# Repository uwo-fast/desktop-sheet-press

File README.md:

# Open Source Scientific Sheet Press: General Overview

This repository contains the design assets for the publication [Open-source cold and hot scientific sheet press for investigating polymer-based material properties](https://doi.org/10.1016/j.ohx.2024.e00566), which details the development of an adaptable, open-source platform for polymer sheet pressing.".

## Description

The Open Source Scientific Sheet Press is a mechanical device engineered for converting plastic waste into flat sheets of recycled plastic. Drawing inspiration from existing models like Precious Plastics, this platform is designed with adaptability, flexibility, and sustainability as core principles. This repository contains the main resources for the design of the physical press and it's manufacturing.

## Key Features

1. **Adaptability**: Engineered to work with a diverse range of plastic materials.
2. **Scalability**: Modular design allows for easy scaling to meet various production needs.
3. **Flexibility**: Utilizes open-source and off-the-shelf components, with comprehensive documentation and multiple system topologies for customization.

## General Applications

1. **Material Recycling**: Transforms plastic waste into reusable sheets.
2. **Product Manufacturing**: Ideal for the production of flat plastic components across various applications.
3. **Research and Development**: Serves as a testbed for material properties and novel production methods.

## Future Directions

1. **5x5' Canadian Standardized Sheet Press**: This version will meet industrial standards within the province of Ontario.
2. **Expanding System Topologies**: Work is ongoing to offer more system variations based on desired specifications and features.
3. **Vacuum Forming Integration**: Plans to incorporate vacuum forming capabilities, expanding the range of products that can be manufactured from the recycled plastic sheets.
4. **Automation and Industry 4.0**: Future iterations will focus on integrating smart technologies for autonomous operation, real-time data analytics, and IoT capabilities.
5. **Comprehensive Sourcing**: Plans to provide sourcing information tailored to various locales, considering regional regulations, standards, and availability.
6. **Reengineering High-Cost Components**: Long-term goal to redesign non-open-source and expensive components to meet required standards and certifications.

## Repository Structure

This repository will include multiple iterations and variations of the sheet press, acting as a living document for continuous development and enhancements.

For detailed documentation, consult the respective folders and files within this repository.

## About the FAST Research Group

The Free Appropriate Sustainable Technology (FAST) research group, led by Professor Joshua Pearce, is based at Western University and focuses on driving sustainability innovations. The group works on a myriad of projects ranging from solar photovoltaic technology to alternative food to open-source hardware to distributed recycling and additive manufacturing (DRAM).

This Open Source Sheet Press project is an initiative led by the FAST group, aligning with our broader goals of sustainable development and open-source technology. We are focused on developing solutions that not only contribute to recycling and sustainable manufacturing but also push the boundaries of what's possible through continuous research and innovation.

For more information on the FAST group, please visit [FAST on Appropedia](https://www.appropedia.org/FAST).

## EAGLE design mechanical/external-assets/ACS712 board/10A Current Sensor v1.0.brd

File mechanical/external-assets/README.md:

# LEGAL DISCLAIMER AND LIMITATION OF LICENSING FOR "EXTERNAL-ASSETS" DIRECTORY

## SCOPE OF DISCLAIMER
This "external-assets" folder is a directory of various third-party materials — software, digital files, and other intellectual properties (hereafter "Assets"). This disclaimer serves as notice that the intellectual property rights governing these Assets are distinctly separate from the GNU General Public License v3.0 (the "Primary License") that applies to the remainder of this repository.

## EXCEPTION TO PRIMARY LICENSE
The Primary License does not extend to the Assets within this directory. Intellectual property rights of each Asset are held by their respective legal owner(s), who reserve all rights not explicitly granted. The inclusion of these Assets within this repository should not be construed as an implicit grant of rights, license, or privileges pertaining to said Assets.

## ATTRIBUTION
For each Asset, an `attribution.txt` document is be available in the respective directory. This document identifies the Asset's original source and, if available, its legal owner, along with any known or asserted intellectual property rights or usage limitations.

## CORRECTIVE MEASURES
If you are the rightful owner of an Asset and suspect a breach of your intellectual property rights within this repository, you are implored to contact the repository owner forthwith. The intent is to promptly remedy any infringement or inadequate attribution as per your rightful demands.

## ABSOLUTE DISCLAIMER OF WARRANTIES
The Assets are furnished "as is," bereft of any warranty, whether overt or implied. The repository owner disclaims all accountability and liability stemming from the use or misuse of these Assets.

## NO AFFILIATION OR ENDORSEMENT
The presence of these Assets within this repository should not be interpreted as an indication of partnership, endorsement, or affiliation between the repository owner and the legal owner(s) of the Assets. All trademarks and identifiers are employed solely for descriptive and attribution purposes.

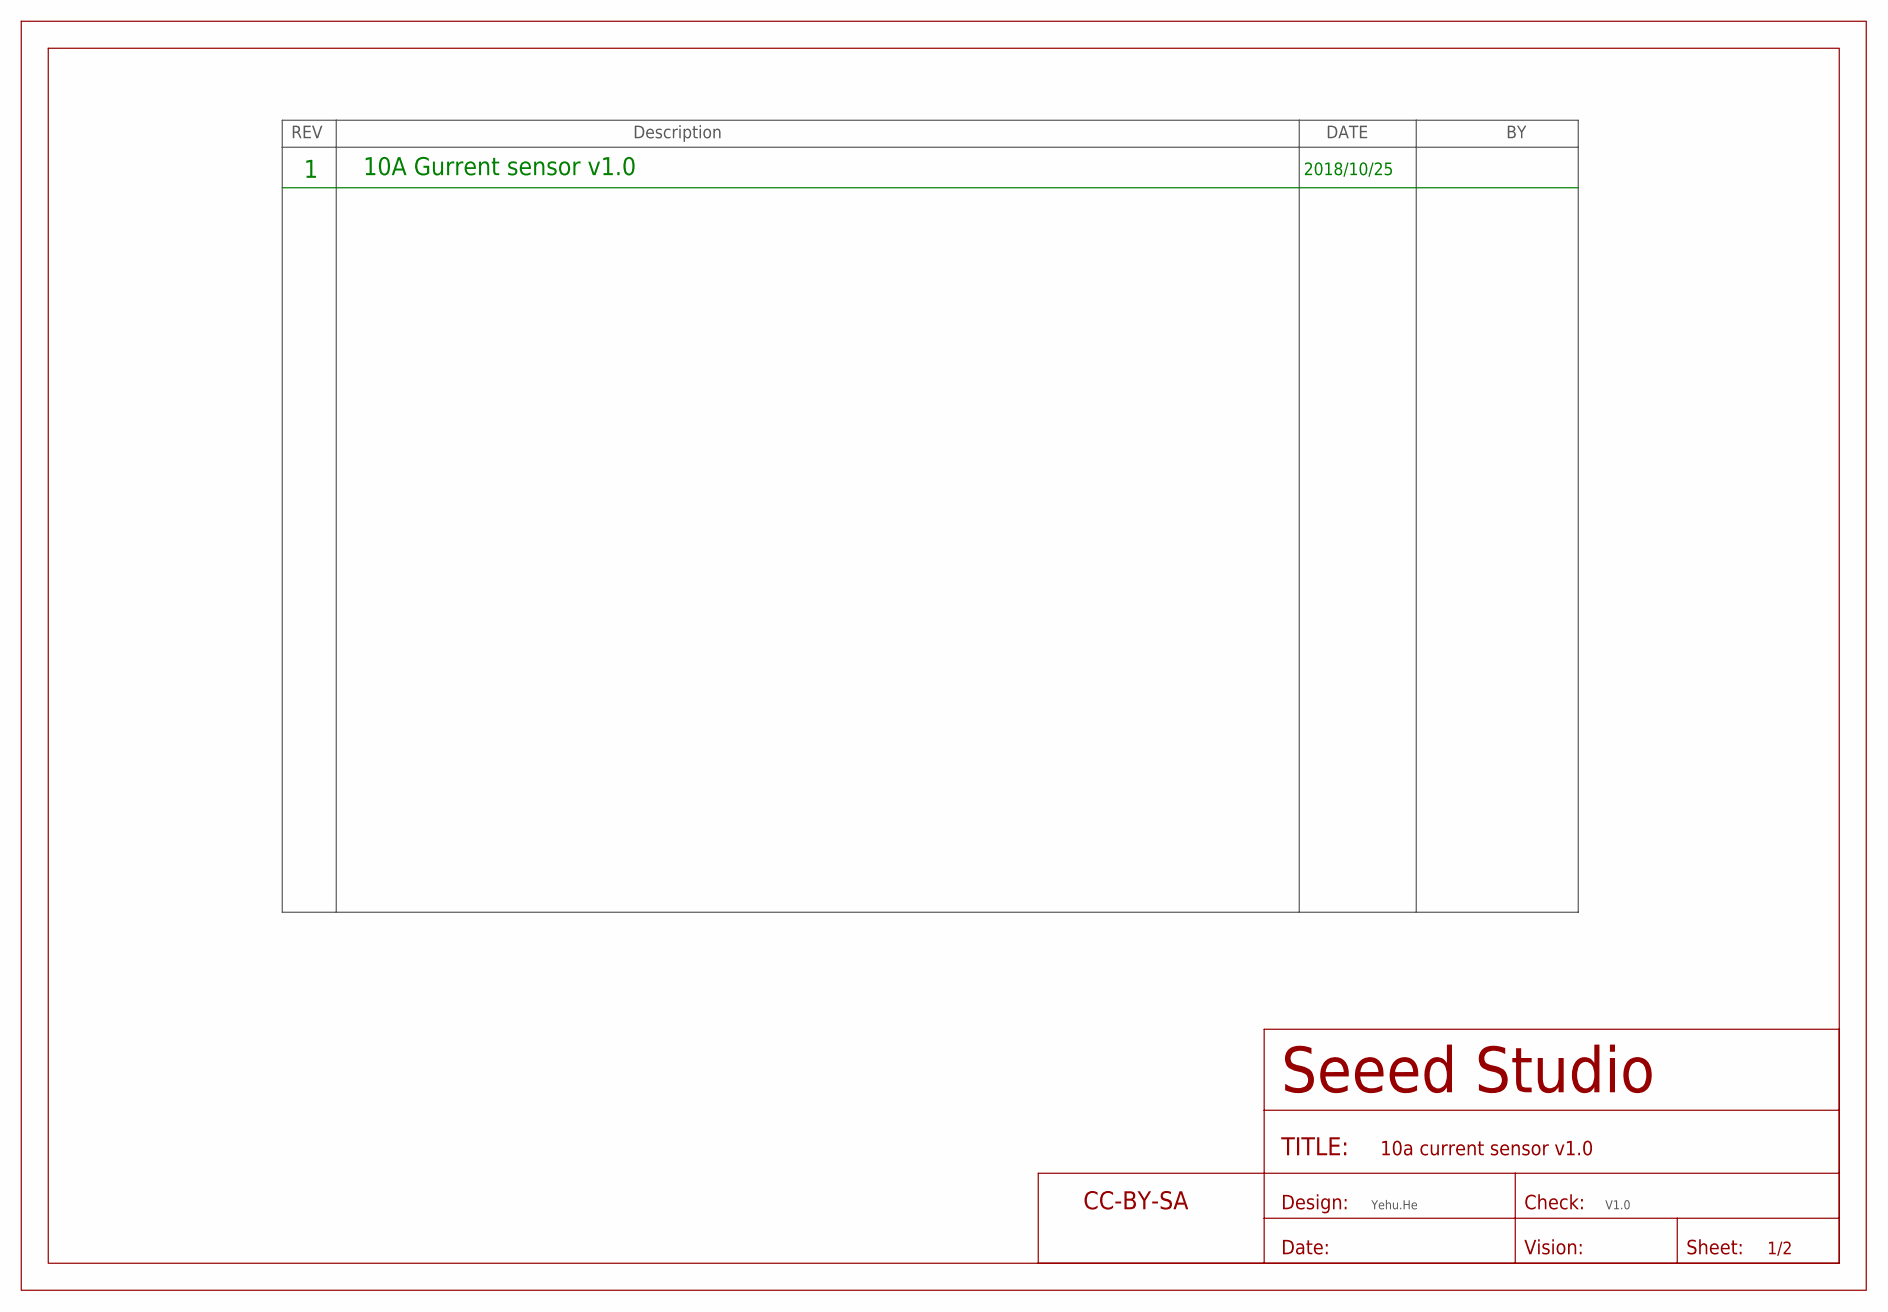
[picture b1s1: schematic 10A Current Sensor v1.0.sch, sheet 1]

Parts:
FR1: SEEEDSTUDIO-OPEN-SCH-FRAME; SEEEDSTUDIO-PCB-FRAME

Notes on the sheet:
Yehu.He
V1.0
10A Gurrent sensor v1.0
2018/10/25

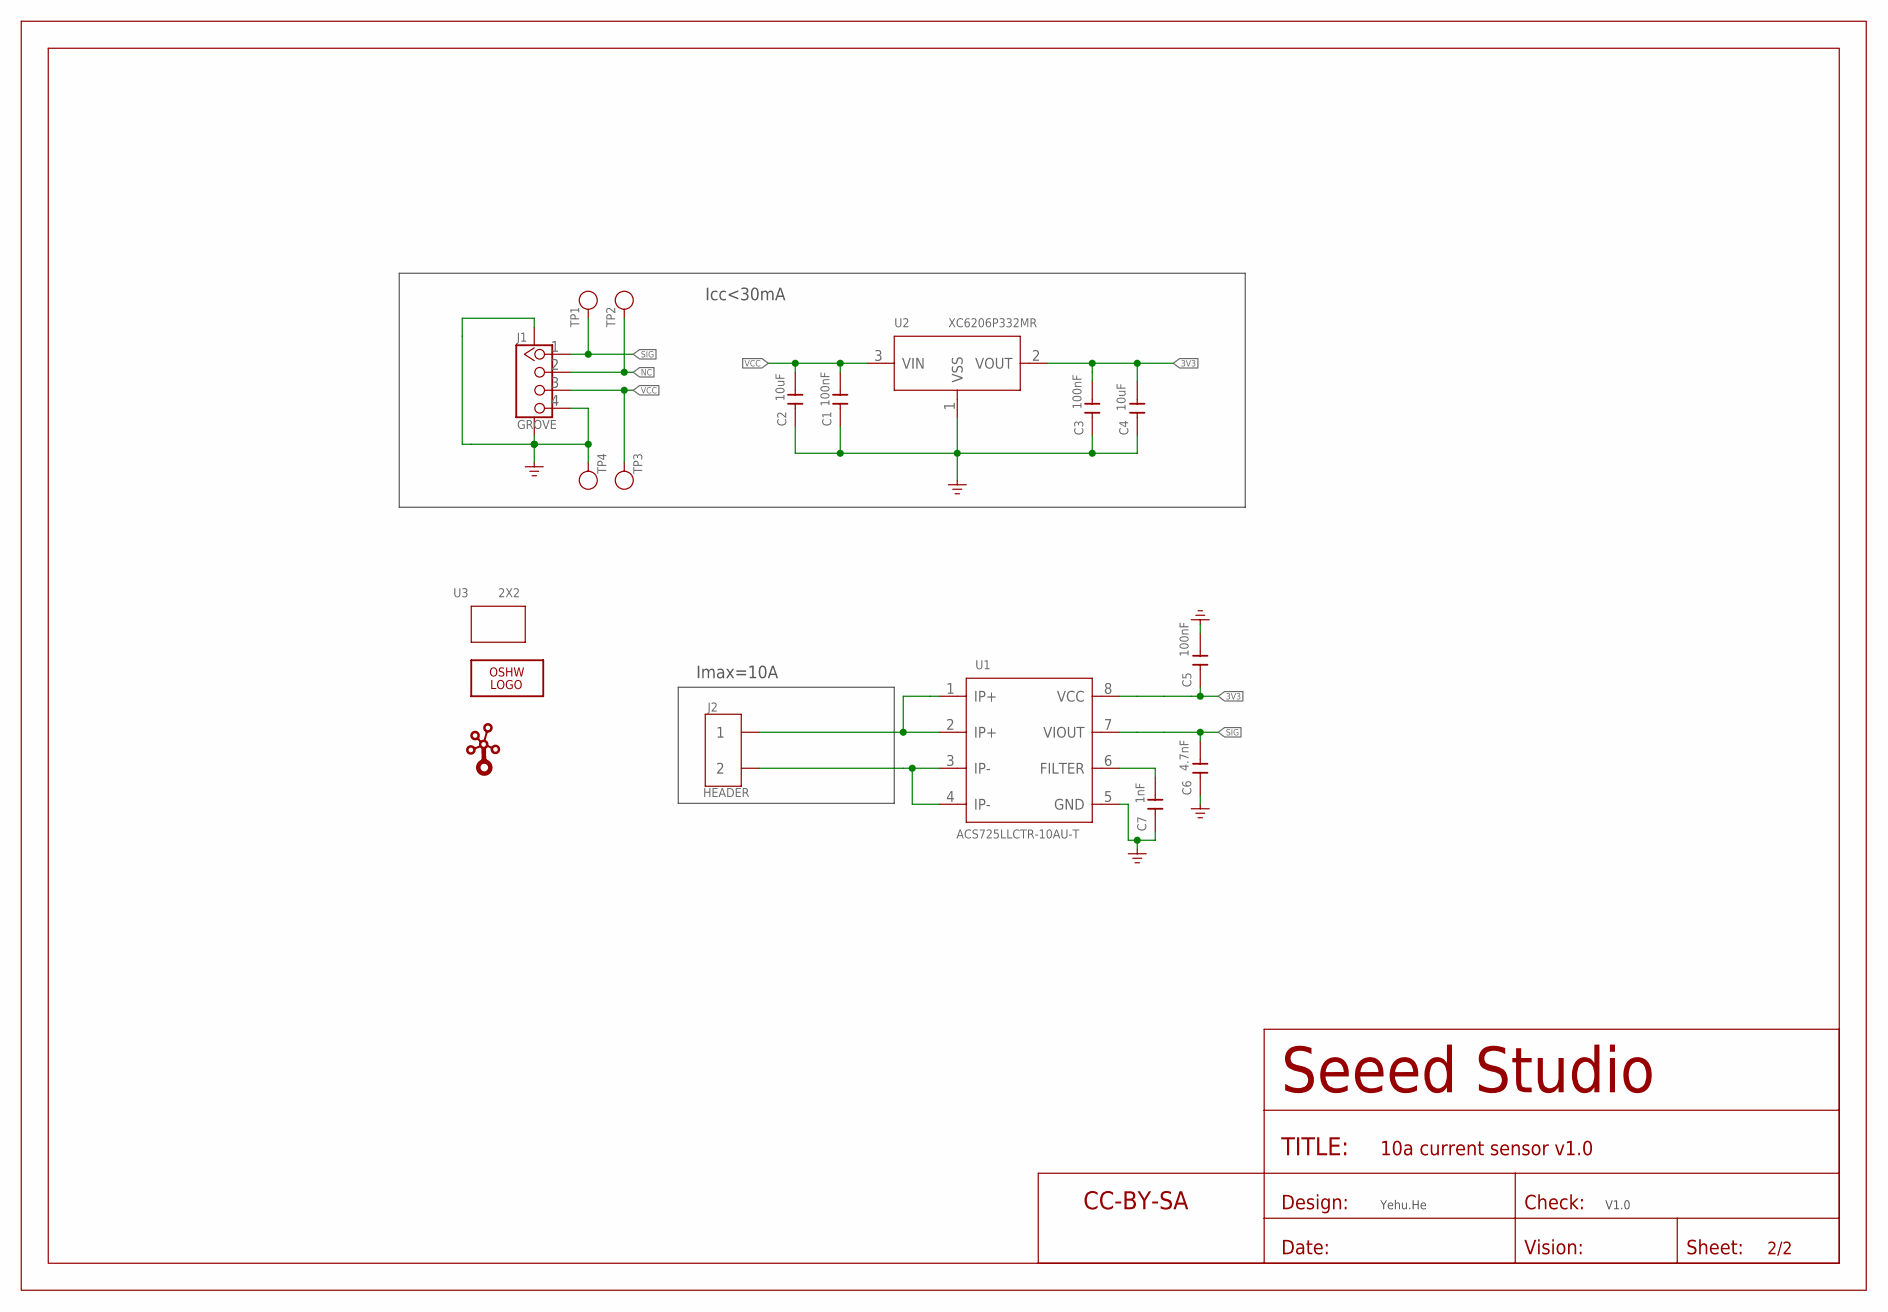
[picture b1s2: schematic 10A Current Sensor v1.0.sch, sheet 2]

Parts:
C1, C3, C5: 100nF; C0603
C2, C4: 10uF; C0603
C6: 4.7nF; C0603
C7: 1nF; C0603
FR2: SEEEDSTUDIO-OPEN-SCH-FRAME; SEEEDSTUDIO-PCB-FRAME
J1: GROVE; HW4-SMD-2.0
J2: HEADER; H2-5.0-10.5X8.0MM
LOGO1: LOGO-OSHW-FILLX0200-NT; OSHW_FILLX200_NOTEXT
TP1, TP2, TP3, TP4: TEST; TP-D45MIL
U1: ACS725LLCTR-10AU-T; SOIC8-1.27-5X4MM
U2: XC6206P332MR; SOT-23
U3: 2X2; GROVE-1*2-TEST-PLATFORM-TOP
U$7: LOGO-GROVE; GROVE-SILK-BIG

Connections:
3V3: C3.2, C4.2, C5.1, U1.8 (VCC), U2.2 (VOUT)
GND: C1.1, C2.1, C3.1, C4.1, C5.2, C6.1, C7.1, J1.4, J1.SS1, J1.SS2, TP4.T, U1.5 (GND), U2.1 (VSS)
unnamed: C7.2, U1.6 (FILTER)
unnamed: J2.2, U1.3 (IP-), U1.4 (IP-)
unnamed: J2.1, U1.1 (IP+), U1.2 (IP+)
NC: J1.2, TP2.T
SIG: C6.2, J1.1, TP1.T, U1.7 (VIOUT)
VCC: C1.2, C2.2, J1.3, TP3.T, U2.3 (VIN)

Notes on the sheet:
Imax=10A
Icc<30mA
Yehu.He
V1.0

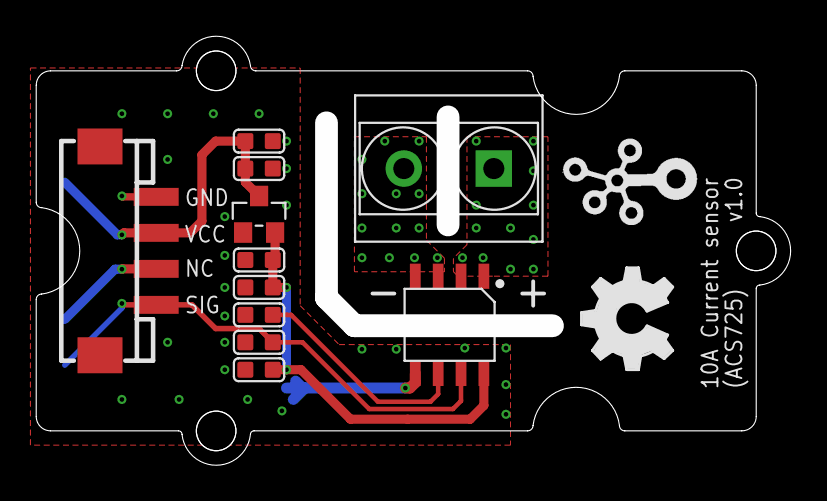
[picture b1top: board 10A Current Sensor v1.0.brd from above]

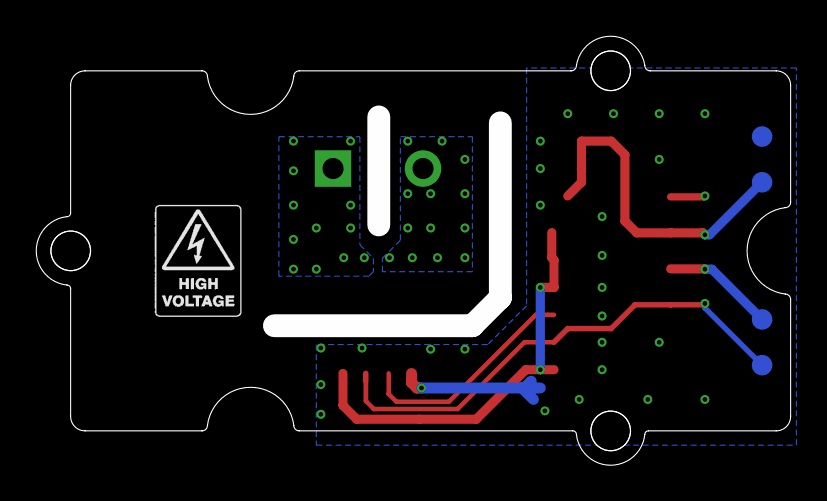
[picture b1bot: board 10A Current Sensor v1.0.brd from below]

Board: 2 copper layers, 40.7 x 22.6 mm, 20 parts (4 on the bottom side), 8 nets.

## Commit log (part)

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2023-09-30 Create .gitignore
    Initial gitignore template
2023-09-30 Delete control-software directory
    Added gitignore, will repush
2023-09-30 Delete electrical-design directory
    Added gitignore, will repush
2023-09-30 Delete mechanical-design directory
    Added gitignore, will repush
2023-09-30 added structural directory
2023-09-30 Delete mechanical-design/OSCHSSP_Mini_Enclosure_v1.1.20230928-190127.FCBak
    FCbak delete
2023-09-30 Delete mechanical-design/OSCHSSP_Mini_Assembly.20230927-000818.FCBak
    FCbak delete
2023-10-08 project set up stuff and alt builds start
2023-10-08 yet more reorganizing and refactoring
2023-10-08 README
2023-10-08 README future directions upgrade
2023-10-08 README FAST stuff
2023-10-08 README tweak
2023-10-08 README tweak final
2023-10-08 README for tp-assets markdown
2023-10-08 removed lines
2023-10-08 README for fixed assets-tp to tp-assets
2023-10-08 reorg anized freecad file structure
2023-10-09 freecad cleaning & started qelectrotech design for industrial
2023-10-13 added readme for industrial opta electrical
2023-10-13 naming fix
2023-10-14 updated auto num readme
2023-10-17 coils for qet file
2023-10-22 updated the electrical schematic opta
2023-10-24 alternative suppliers
2023-10-24 sourcing components
2023-11-01 separated industrial into own repo
2023-11-01 Update README.md for scientific specifier
2023-11-02 enabled lfs for step and stl files
2023-11-09 added flow diagram mermaid js in jupyter
2023-11-12 added algo charts
2023-11-12 Upload New File
2023-12-05 updated the core software builds and added algorithm charts
2023-12-23 check push
2024-01-26 initial commit of prudentia
2024-01-26 added snap fit geo using openscad
2024-01-28 more work on the prudentia enclosure
2024-02-14 updated enclosure and added 2 DoF attachment
2024-02-20 local push
2024-02-23 printable enclosure for paper
2024-02-24 updated steps & stl for paper
2024-02-27 updated enclosure
2024-02-27 added file for updated electrical
2024-02-27 cleaned up elec dir
2024-02-28 assembly organization for easier CAD nav
2024-02-29 updated and organized files
2024-03-01 updates for paper
2024-03-05 edits to software
2024-03-08 did some more clean up and gui
2024-03-09 finishing up header for clarity
2024-03-10 updated elec
2024-03-11 added full depth to electrical and software segmentation
2024-03-11 splitting off of archives into dedicated dev archive
2024-03-12 updates to elec
2024-03-13 updates to ui
2024-03-14 updated ui
2024-03-18 rotary action gui changes
2024-03-19 optimized ram usage using PROGMEM for lcd strings
2024-04-06 version 1.1.0 adds header var for using 1 TC, fixes to uint vars
2024-04-27 v2 of elec separating gui and improved part selection
2024-05-08 minor organizational changes for paper
2024-05-22 schematic updates
2024-07-01 thermocouple non sense
2024-07-03 split in progress
2024-07-04 initial split and archived past
2024-07-15 Added Press_Software_Flow_Diagram.drawio
2024-07-30 Generalization and clean up
2024-08-20 rewrote thermal runaway as a class and improved clarify and operational logic
2024-08-21 cleaned things up by adding getters/setters and templates
2024-08-22 added to LCD
2024-08-26 Added back elec and software as submodules to new repos
2024-08-26 added todos and info to readmes in subdirs
2024-08-27 added usage docs for gui and cmd usage and cleared redundant state commands
2024-12-02 cleaned up organization and better implemented separation of concerns and best practices of modular programming where relevant
2024-12-03 cleaned up and minimized
2024-12-03 further reduced memory footprint, even more organization, only to find out the nan was just being propagated from TC measure
2025-02-03 added info linking to onshape enclosure
2025-02-03 added back from osf
2025-02-03 organized docs and moved procurement
2025-02-04 Remove .gitattributes and LFS tracking
2025-02-04 fixed readme
2025-02-04 minor updates
2025-02-11 added a sudo mode for easier testing
2025-02-11 minor fixes
2025-02-11 fixed writeRelay function correct const mismatch
2025-02-12 added phase implementation
2025-02-26 updated src readme
2025-02-27 added notes
2025-02-27 press config update
2025-02-27 added pid interval to all
2025-05-09 some clean up and reorganizing, added limiting and adaptive pid
2025-05-09 fixed some bugs

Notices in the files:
parts and their libraries:
moudle-new: This work is licensed under the Creative Commons Attribution 4.0 International License.
To view a copy of this license,visit:
http://creativecommons.org/licenses/by-sa/4.0
moudle-new: CC-BY-SA
